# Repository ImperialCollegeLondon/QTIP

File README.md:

# Quadrotor Topped Inverted Pendulum (QTIP)

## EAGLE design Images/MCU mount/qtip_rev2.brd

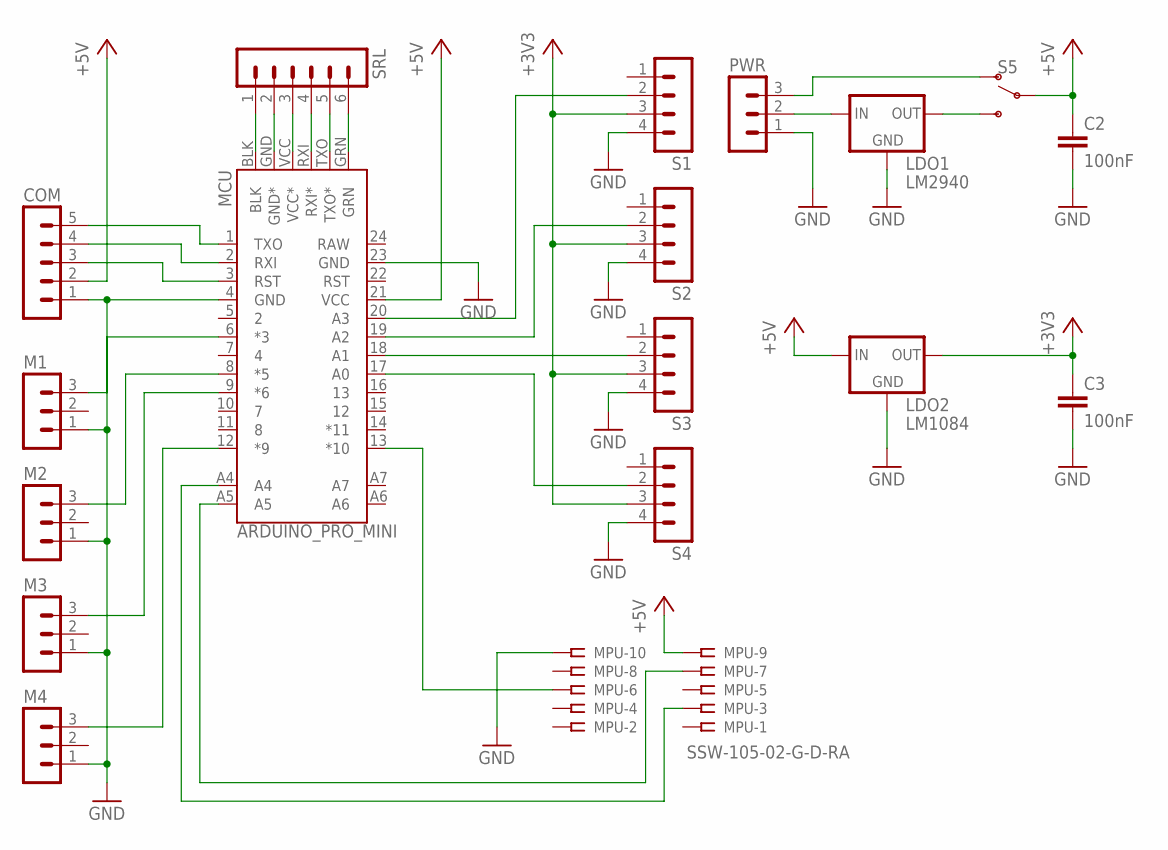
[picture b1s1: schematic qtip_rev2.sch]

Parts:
C2, C3: 100nF; C025-024X044
COM: MA05-1
LDO1: LM2940; 78XXL
LDO2: LM1084; 78XXL
M1, M2, M3, M4: MA03-1
MCU: ARDUINO_PRO_MINI
MPU: SSW-105-02-G-D-RA
PWR: MA03-1
S1, S2, S3, S4: MA04-1
S5: SWITCH-SPDT-PTH-11.6X4.0MM; SWITCH_SPDT_PTH_11.6X4.0MM
SRL: MA06-1

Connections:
+3V3: C3.1, LDO2.GND (OUT), S1.3, S2.3, S3.3, S4.3
+5V: C2.1, COM.2, LDO2.OUT (IN), MCU.21 (VCC), MPU.9, S5.2
GND: C2.2, C3.2, COM.1, LDO1.IN (GND), LDO2.IN (GND), M1.1, M2.1, M3.1, M4.1, MCU.4 (GND), MCU.23 (GND), MPU.10, PWR.1, S1.4, S2.4, S3.4, S4.4
MV2: M2.3, MCU.8 (*5)
unnamed: MCU.A5, MPU.7
unnamed: MCU.A4, MPU.3
unnamed: MCU.20 (A3), S1.2
unnamed: MCU.13 (*10), MPU.6
unnamed: MCU.17 (A0), S4.2
unnamed: M1.3, MCU.6 (*3)
unnamed: M4.3, MCU.12 (*9)
unnamed: M3.3, MCU.9 (*6)
unnamed: LDO1.OUT (IN), PWR.2
unnamed: MCU.BLK, SRL.1
unnamed: COM.5, MCU.1 (TXO)
unnamed: COM.4, MCU.2 (RXI)
unnamed: COM.3, MCU.3 (RST)
unnamed: MCU.GND (GND*), SRL.2
unnamed: MCU.18 (A1), S3.2
unnamed: MCU.VCC (VCC*), SRL.3
unnamed: MCU.19 (A2), S2.2
unnamed: MCU.RXI (RXI*), SRL.4
unnamed: LDO1.GND (OUT), S5.3 (S)
unnamed: MCU.TXO (TXO*), SRL.5
unnamed: PWR.3, S5.1 (O)
unnamed: MCU.GRN, SRL.6
RAW: MCU.24 (RAW)

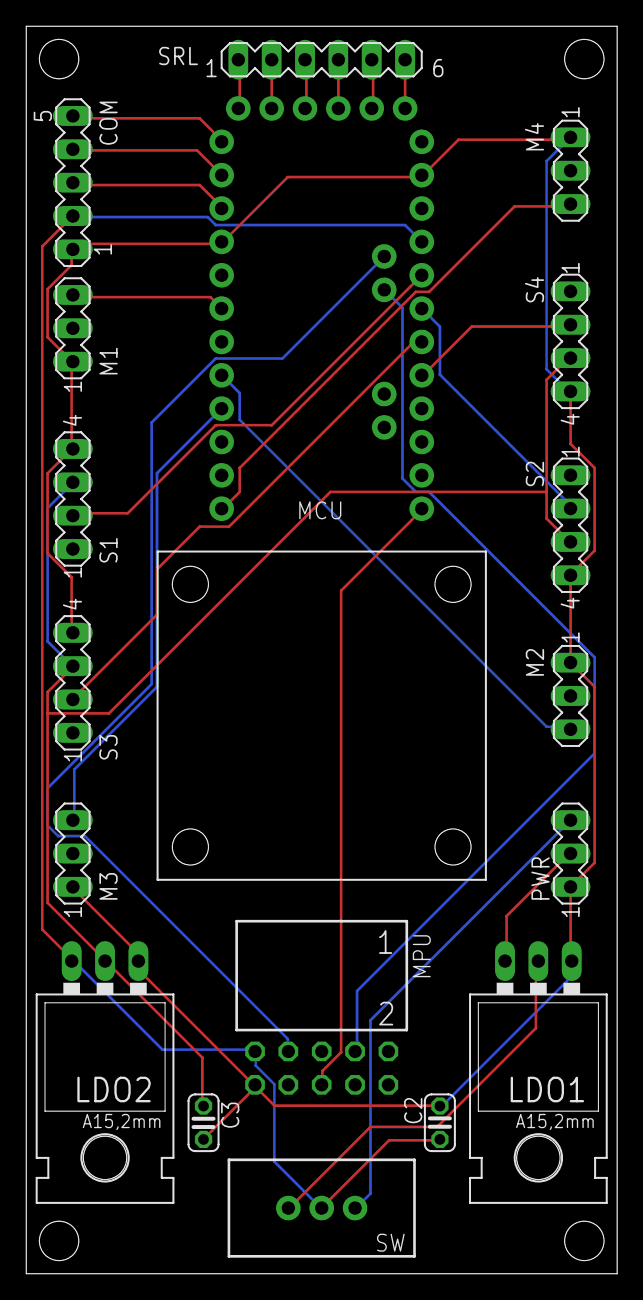
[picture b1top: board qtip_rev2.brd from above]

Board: 2 copper layers, 45.0 x 95.0 mm, 18 parts (0 on the bottom side), 26 nets.

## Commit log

2018-06-27 Add files via upload
    I tried to have the files in different formats, but fusion failed all translations except for fusion files.
2018-09-14 Arduino Code and Images upload
2018-09-26 All files upload
    Cleaned all files up
2019-04-26 MPU tester code optimised for Arduino Pro Mini 328
2019-04-26 Old MPUTest obsolete
2019-04-26 MPUTest optimised
2019-04-26 PID Controller optimised for Arduino Pro Mini 328
2019-04-26 MCU and MPU mount board schematics upload
    compatible with Autodesk Eagle 9.x.x
2019-04-26 Board and schematics images upload
2019-04-29 PCB design revision 2 + PCB design files upload
2019-06-25 PID controller with serial comms
2019-06-25 MPU calibration sketch bug fix
    now it actually calibrates the DMP offsets
2019-07-01 Test files final update + reorganised folder
2019-07-01 Final test sketches update / directory reorganised
2019-07-01 Final files update since JYP project
2019-07-01 Reorganise folder
2019-07-01 Controller designer MATLAB scripts upload
2019-07-01 Test data used in project (PARK)
2019-07-10 Jee Yong Park deliverables upload

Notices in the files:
parts and their libraries:
SparkFun-IC-Power: Licensing: Creative Commons ShareAlike 4.0 International - https://creativecommons.org/licenses/by-sa/4.0
